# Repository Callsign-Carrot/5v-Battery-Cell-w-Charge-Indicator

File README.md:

# 5v-Battery-Cell-w-Charge-Indicator
<h3>5v Battery cell inspired by Subnautica and Titanfall.</h3>

<p>This is a project that turns boring batteries into a satisfying mechanisim. Inspired by games like Subnautica and Titanfall, you simply insert and twist to plug it in. Designed to last a long time for circuits running 5v at < 1.5A. This circuit includes a <a href="https://www.ti.com/lit/ds/symlink/tps61023.pdf?HQS=dis-dk-null-digikeymode-dsf-pf-null-wwe&ts=1617863529482">TSP61023 boost converter</a>, <a href="https://www.mouser.com/datasheet/2/268/AVR32_16DD20_14_Prel_DataSheet_DS40002413-2997818.pdf">AVR16DD14 microcontroller</a>, and a <a href="https://www.analog.com/media/en/technical-documentation/data-sheets/MAX17048-MAX17049.pdf">MAX17048 Fuel gauge</a>. Device also features <a href="https://cdn-shop.adafruit.com/product-files/2686/SK6812MINI_REV.01-1-2.pdf">SK6812MINI RGB LEDs</a> for the outward facing indicator.</p>
<h5>Planned Features</h5>
<ul>
  <li>3D Model (already *mostly* done)</li>
  <li>Programming (Not even started :D)</li>
  <li>Animations for inidcator</li>
</ul>
<h3>ONLY USE PROTECTED LI-POs WITH THIS CIRCUIT :D</h3>
<div>
<h3>Circuit diagram</h3>

<h3>Front of circuit board</h3>

<h3>Back of circuit board</h3>

</div>

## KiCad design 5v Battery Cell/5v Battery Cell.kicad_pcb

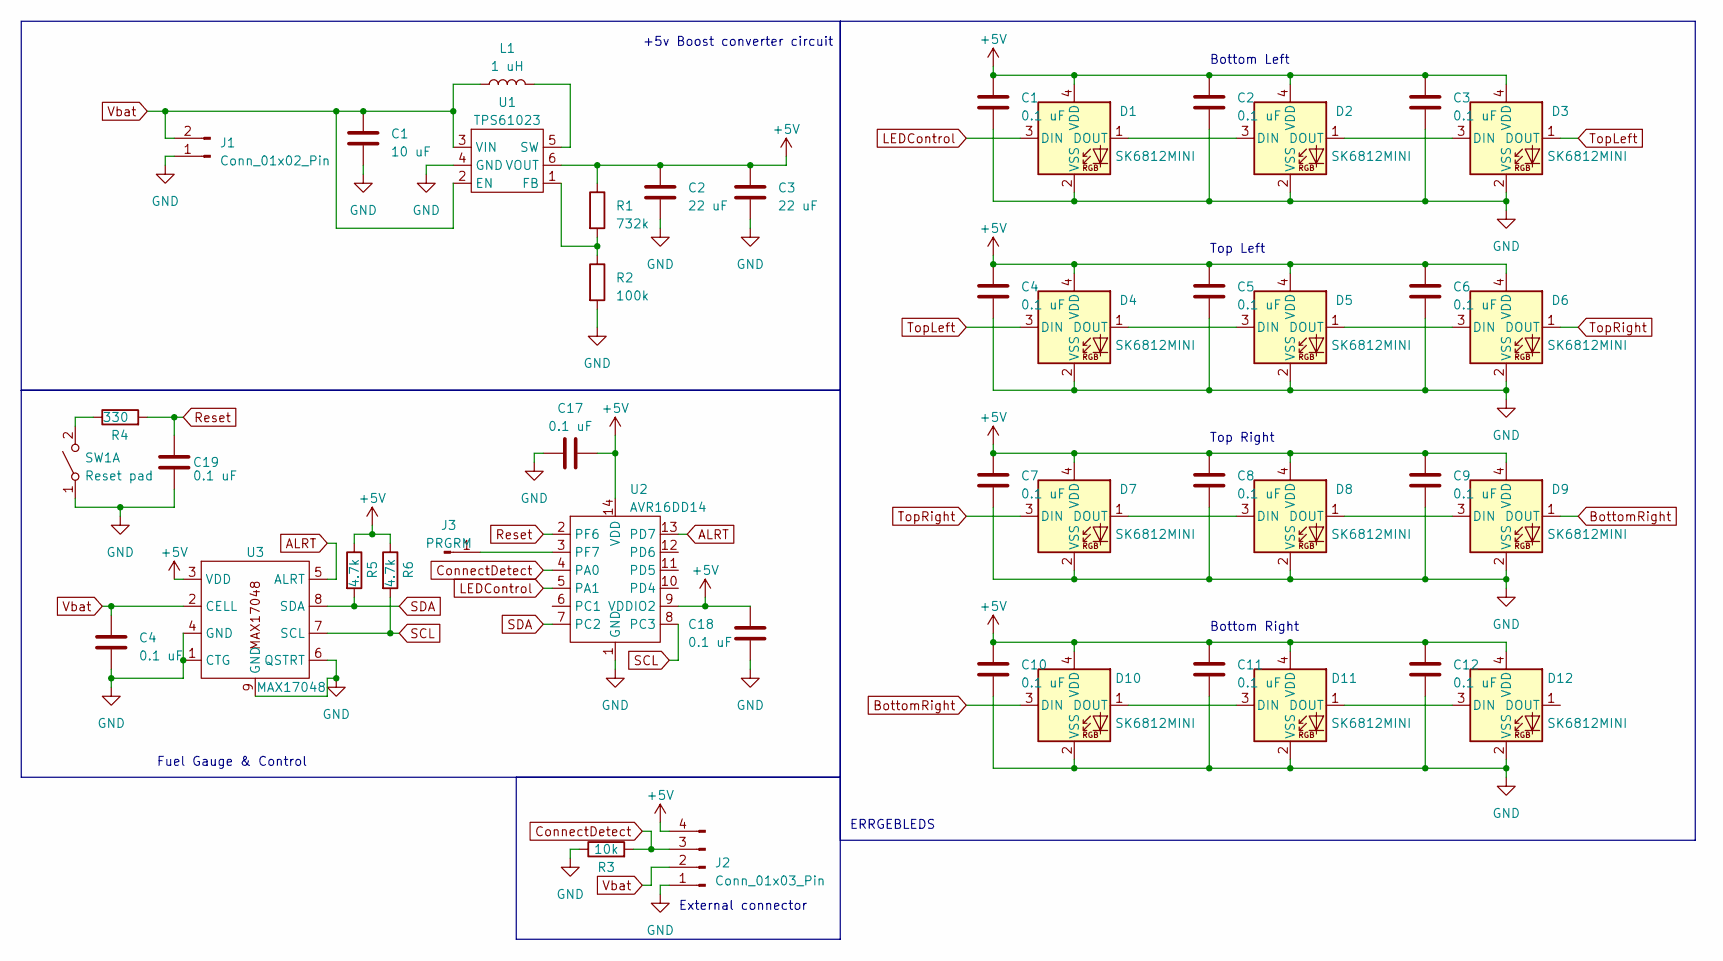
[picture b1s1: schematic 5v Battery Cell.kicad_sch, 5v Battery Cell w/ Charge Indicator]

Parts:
C1: 10 uF; C_0603_1608Metric_Pad1.08x0.95mm_HandSolder
C2: 22 uF; C_0603_1608Metric_Pad1.08x0.95mm_HandSolder
C3, C4, C5, C6, C7, C8, C9, C10, C11, C12, C17, C18, C19: 0.1 uF; C_0603_1608Metric_Pad1.08x0.95mm_HandSolder
D1, D2, D3, D4, D5, D6, D7, D8, D9, D10, D11, D12: SK6812MINI; LED_SK6812MINI_PLCC4_3.5x3.5mm_P1.75mm
J1: Conn_01x02_Pin; JST_PH_S2B-PH-K_1x02_P2.00mm_Horizontal
J2: Conn_01x03_Pin; PinSocket_1x04_P2.54mm_Vertical
J3: PRGRM; Pin_D0.7mm_L6.5mm_W1.8mm_FlatFork
L1: 1 uH; L_0805_2012Metric_Pad1.05x1.20mm_HandSolder
R1: 732k; R_0603_1608Metric_Pad0.98x0.95mm_HandSolder
R2: 100k; R_0603_1608Metric_Pad0.98x0.95mm_HandSolder
R3: 10k; R_0603_1608Metric_Pad0.98x0.95mm_HandSolder
R4: 330; R_0603_1608Metric_Pad0.98x0.95mm_HandSolder
R5, R6: 4.7k; R_0603_1608Metric_Pad0.98x0.95mm_HandSolder
SW1: Reset pad; R_0603_1608Metric_Pad0.98x0.95mm_HandSolder
U1: TPS61023; SOT-563
U2: AVR16DD14; SOIC-14_3.9x8.7mm_P1.27mm
U3: MAX17048; TDFN-8-1EP_2x2mm_P0.5mm_EP0.8x1.2mm

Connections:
ALRT: U2.13 (PD7), U3.5 (ALRT)
BottomRight: D9.1 (DOUT), D10.3 (DIN)
ConnectDetect: J2.3, R3.2, U2.4 (PA0)
GND: C1.2, C2.2, C3.2, C4.2, C5.2, C6.2, C7.2, C8.2, C9.2, C10.2, C11.2, C12.2, C17.1, C18.2, C19.1, D1.2 (VSS), D2.2 (VSS), D3.2 (VSS), D4.2 (VSS), D5.2 (VSS), D6.2 (VSS), D7.2 (VSS), D8.2 (VSS), D9.2 (VSS), D10.2 (VSS), D11.2 (VSS), D12.2 (VSS), J1.1, J2.1, R2.2, R3.1, SW1.1 (A), U1.4 (GND), U2.1 (GND), U3.1 (CTG), U3.4 (GND), U3.6 (QSTRT), U3.9 (GND); also elsewhere on the board
LEDControl: D1.3 (DIN), U2.5 (PA1)
unnamed: D1.1 (DOUT), D2.3 (DIN)
unnamed: D2.1 (DOUT), D3.3 (DIN)
unnamed: D4.1 (DOUT), D5.3 (DIN)
unnamed: D5.1 (DOUT), D6.3 (DIN)
unnamed: D7.1 (DOUT), D8.3 (DIN)
unnamed: D8.1 (DOUT), D9.3 (DIN)
unnamed: D10.1 (DOUT), D11.3 (DIN)
unnamed: D11.1 (DOUT), D12.3 (DIN)
unnamed: J3.1, U2.3 (PF7)
unnamed 14: R4.1, SW1.2 (B); also elsewhere on the board
unnamed: R1.2, R2.1, U1.1 (FB)
unnamed: L1.2, U1.5 (SW)
Reset: C19.2, R4.2, U2.2 (PF6)
SCL: R6.2, U2.8 (PC3), U3.7 (SCL)
SDA: R5.2, U2.7 (PC2), U3.8 (SDA)
TopLeft: D3.1 (DOUT), D4.3 (DIN)
TopRight: D6.1 (DOUT), D7.3 (DIN)

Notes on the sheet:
Bottom Left
Top Right
Fuel Gauge & Control
ERRGEBLEDS
Top Left
Bottom Right
+5v Boost converter circuit
External connector

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
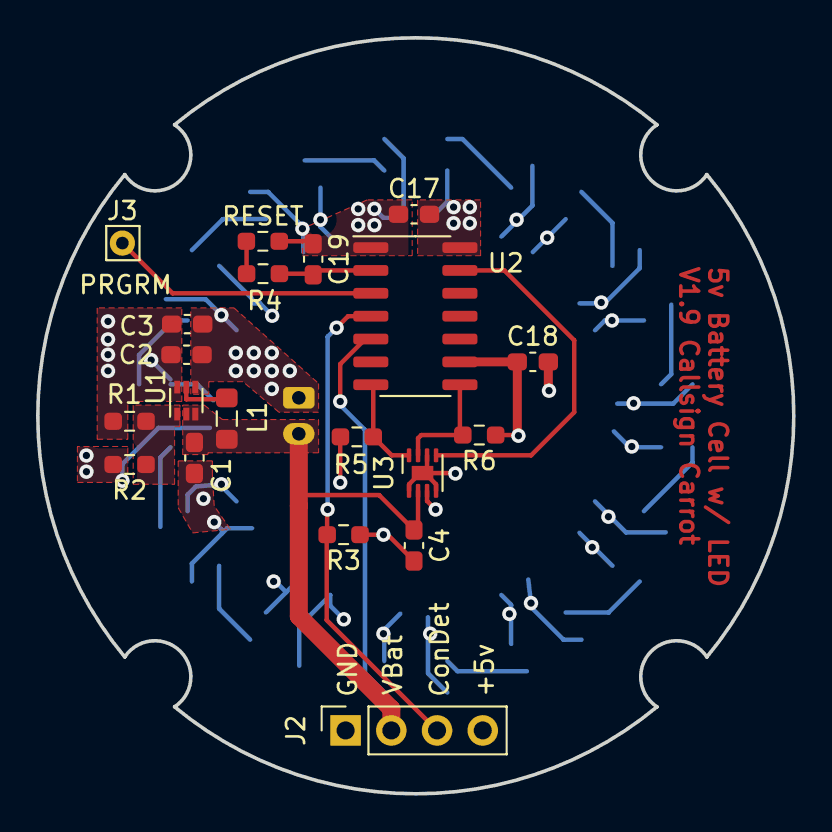
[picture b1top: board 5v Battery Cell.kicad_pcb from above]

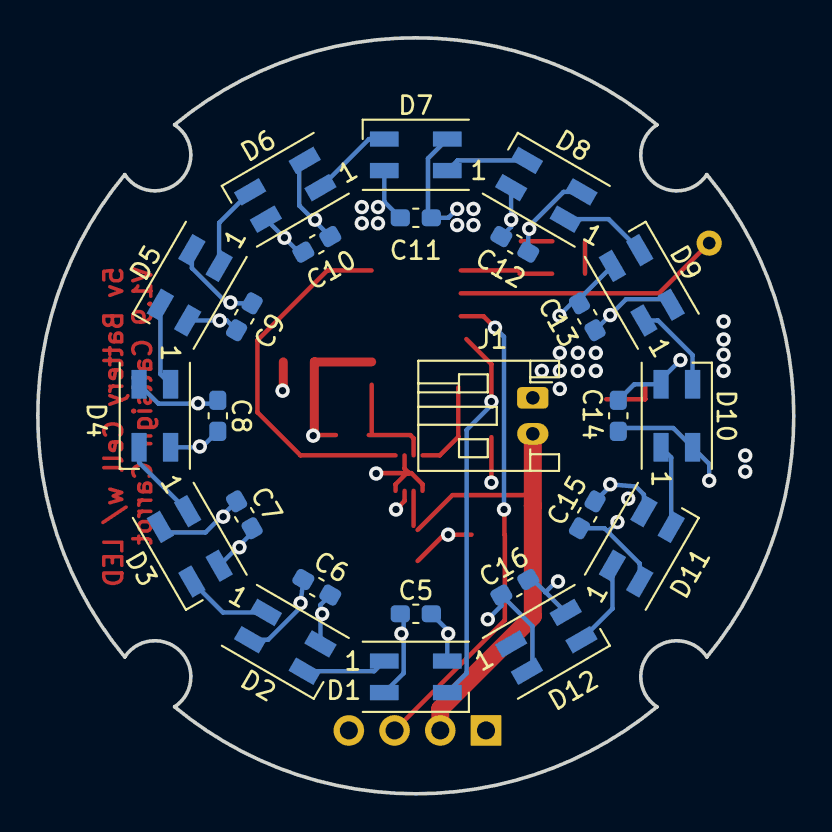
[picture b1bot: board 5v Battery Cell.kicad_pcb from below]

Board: 4 copper layers, 42.0 x 42.0 mm, 45 parts (25 on the bottom side), 24 nets.

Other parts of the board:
C13, C14, C15, C16: 0.1 uF; C_0603_1608Metric_Pad1.08x0.95mm_HandSolder
RESET: Reset pad; R_0603_1608Metric_Pad0.98x0.95mm_HandSolder

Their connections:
GND: C13.2, C14.2, C15.2, C16.2, RESET.1 (A); also elsewhere on the board
unnamed 14: RESET.2 (B); also elsewhere on the board

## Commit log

2023-03-14 Initial file upload.
    Uploaded first "finished" version of the project to share.
2023-03-17 Major revisions to the circuit and PCB design.
    Swapped out the ATTiny204 for the AVR16DD14. Gives me extra room to work with. Updated PCB to actually be able to handle 1.5A draw from the battery, though it's never expected to reach that.
2023-03-17 Updated issue dates.
2023-03-17 Added pretty pictures to the README
